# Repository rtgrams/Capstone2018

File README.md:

# Capstone2018

A collection of PCB designs pertaining to the development of a Multi-Room Smart Vent System during the 2017-2018 academic year.

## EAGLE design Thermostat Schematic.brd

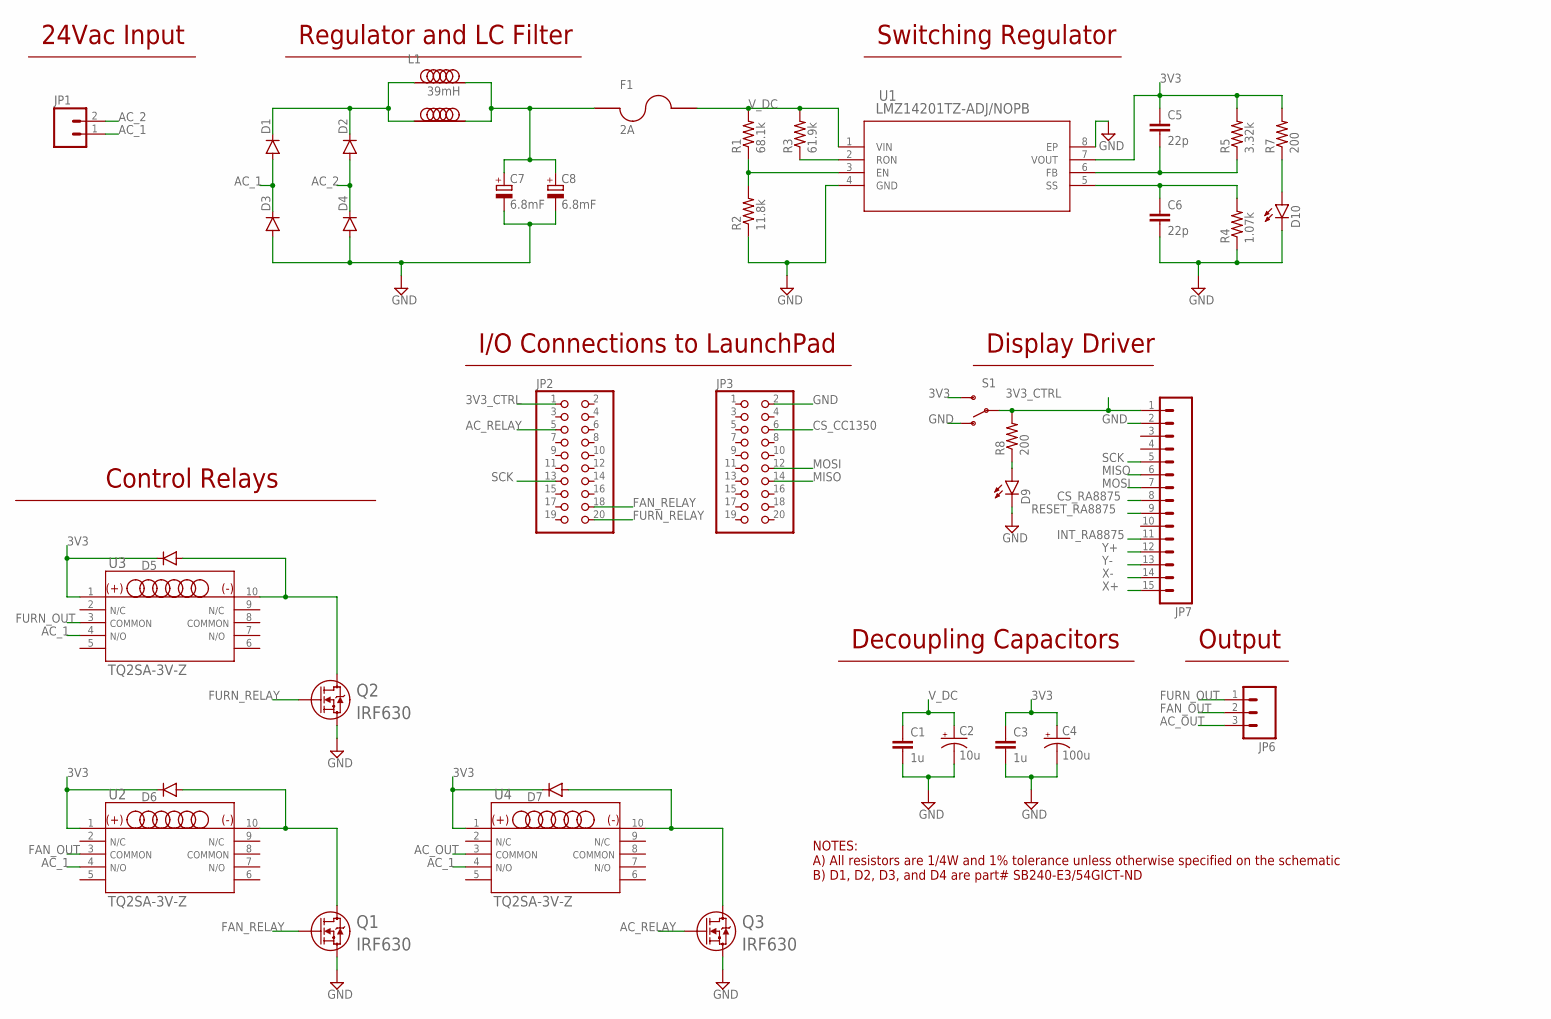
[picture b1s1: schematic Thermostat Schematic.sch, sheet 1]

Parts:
C1, C3: 1u; CAP-PTH-5MM
C2: 10u; CPOL-RADIAL-10UF-25V
C4: 100u; CPOL-RADIAL-1000UF-25V
C5, C6: 22p; CAP-PTH-5MM
C7, C8: 6.8mF; E7,5-16
D1, D2, D3, D4, D5, D6, D7: DIODEPTH; DIODE-1N4001
D9, D10: LED1206; LED-1206
F1: 2A; 36-3550-2-ND
JP1: M023.5MM; SCREWTERMINAL-3.5MM-2
JP2, JP3: PINHD-2X10; 2X10
JP6: M03SCREW; SCREWTERMINAL-3.5MM-3
JP7: M15; 1X15
L1: 39mH; B82733F
Q1, Q2, Q3: IRF630; TO-220
R1: 68.1k; AXIAL-0.3
R2: 11.8k; AXIAL-0.3
R3: 61.9k; AXIAL-0.3
R4: 1.07k; AXIAL-0.3
R5: 3.32k; AXIAL-0.3
R7, R8: 200; AXIAL-0.3
S1: SWITCH-SPDTPTH; SWITCH-SPDT
U1: LMZ14201TZ-ADJ/NOPB; TZA07A
U2, U3, U4: TQ2SA-3V-Z; RELAY_TQ2_SA-M

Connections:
3V3: C3.1, C4.+, C5.1, D5.C, D6.C, D7.C, R5.P$2 (2), R7.P$2 (2), S1.3 (S), U1.7 (VOUT), U2.1, U3.1, U4.1; also elsewhere on the board
3V3_CTRL: JP2.1, JP7.1, R8.P$2 (2), S1.2
AC_1: D1.A, D3.C, JP1.1, U2.4, U3.4, U4.4
AC_2: D2.A, D4.C, JP1.2
AC_OUT: JP6.3, U4.3
AC_RELAY: JP2.5, Q3.1
CS_CC1350: JP3.6; also elsewhere on the board
CS_RA8875: JP7.8; also elsewhere on the board
FAN_OUT: JP6.2, U2.3
FAN_RELAY: JP2.18, Q1.1
FURN_OUT: JP6.1, U3.3
FURN_RELAY: JP2.20, Q2.1
GND: C1.2, C2.2 (-), C3.2, C4.-, C6.2, C7.-, C8.-, D3.A, D4.A, D9.C, D10.C, JP3.2, JP7.2, Q1.3, Q2.3, Q3.3, R2.P$1 (1), R4.P$1 (1), S1.1 (O), U1.4 (GND), U1.8 (EP); also elsewhere on the board
INT_RA8875: JP7.11; also elsewhere on the board
MISO: JP3.14, JP7.6; also elsewhere on the board
MOSI: JP3.12, JP7.7; also elsewhere on the board
unnamed: R1.P$1 (1), R2.P$2 (2), U1.3 (EN)
unnamed: R3.P$1 (1), U1.2 (RON)
unnamed: C5.2, R5.P$1 (1), U1.6 (FB)
unnamed: C6.1, R4.P$2 (2), U1.5 (SS)
unnamed: D9.A, R8.P$1 (1)
unnamed: D1.C, D2.C, L1.P$1, L1.P$4
unnamed: C7.+, C8.+, F1.PIN1A (PIN1), F1.PIN1B (PIN1), L1.P$2, L1.P$3
unnamed: D10.A, R7.P$1 (1)
unnamed: D5.A, Q2.2, U3.10
unnamed: D6.A, Q1.2, U2.10
unnamed: D7.A, Q3.2, U4.10
RESET_RA8875: JP7.9; also elsewhere on the board
SCK: JP2.13, JP7.5; also elsewhere on the board
V_DC: C1.1, C2.1 (+), F1.PIN2A (PIN2), F1.PIN2B (PIN2), R1.P$2 (2), R3.P$2 (2), U1.1 (VIN)
X+: JP7.15; also elsewhere on the board
X-: JP7.14; also elsewhere on the board
Y+: JP7.12; also elsewhere on the board
Y-: JP7.13; also elsewhere on the board

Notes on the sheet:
Decoupling Capacitors
NOTES: A) All resistors are 1/4W and 1% tolerance unless otherwise specified on the schematic B) D1, D2, D3, and D4 are part# SB240-E3/54GICT-ND
I/O Connections to LaunchPad
Regulator and LC Filter
Switching Regulator
24Vac Input
Display Driver
Control Relays
Output

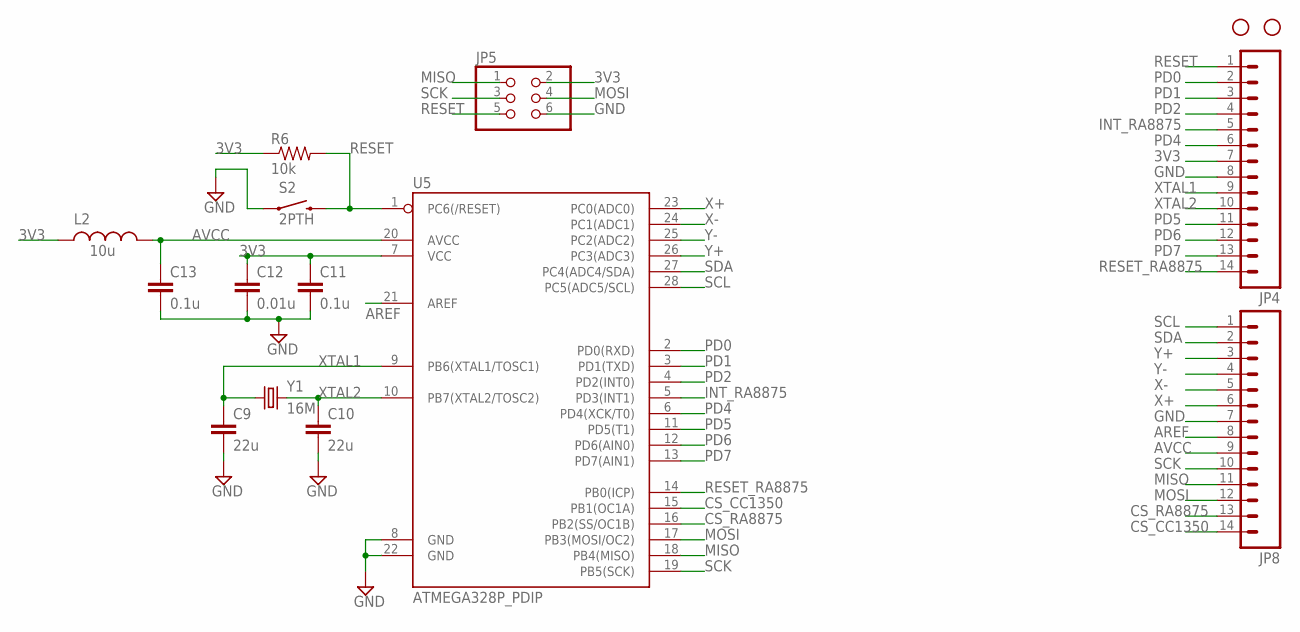
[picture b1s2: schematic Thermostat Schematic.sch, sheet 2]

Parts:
C9, C10: 22u; CAP-PTH-5MM
C11, C13: 0.1u; CAP-PTH-5MM
C12: 0.01u; CAP-PTH-5MM
JP4, JP8: M14; 1X14
JP5: PINHD-2X3; 2X03
L2: 10u; AXIAL-0.6
R6: 10k; AXIAL-0.3
S2: 2PTH; TACTILE-PTH-EZ
STANDOFF3, STANDOFF4: STAND-OFFTIGHT; STAND-OFF-TIGHT
U5: ATMEGA328P_PDIP; DIL28-3
Y1: 16M; HC49US

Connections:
3V3: C11.1, C12.1, JP4.7, JP5.2, L2.P$1 (1), R6.P$1 (1), U5.7 (VCC); also elsewhere on the board
AREF: JP8.8, U5.21 (AREF)
AVCC: C13.1, JP8.9, L2.P$2 (2), U5.20 (AVCC)
CS_CC1350: JP8.14, U5.15 (PB1(OC1A)); also elsewhere on the board
CS_RA8875: JP8.13, U5.16 (PB2(SS/OC1B)); also elsewhere on the board
GND: C9.2, C10.2, C11.2, C12.2, C13.2, JP4.8, JP5.6, JP8.7, S2.1, U5.8 (GND), U5.22 (GND); also elsewhere on the board
INT_RA8875: JP4.5, U5.5 (PD3(INT1)); also elsewhere on the board
MISO: JP5.1, JP8.11, U5.18 (PB4(MISO)); also elsewhere on the board
MOSI: JP5.4, JP8.12, U5.17 (PB3(MOSI/OC2)); also elsewhere on the board
PD0: JP4.2, U5.2 (PD0(RXD))
PD1: JP4.3, U5.3 (PD1(TXD))
PD2: JP4.4, U5.4 (PD2(INT0))
PD4: JP4.6, U5.6 (PD4(XCK/T0))
PD5: JP4.11, U5.11 (PD5(T1))
PD6: JP4.12, U5.12 (PD6(AIN0))
PD7: JP4.13, U5.13 (PD7(AIN1))
RESET: JP4.1, JP5.5, R6.P$2 (2), S2.3 (2), U5.1 (PC6(/RESET))
RESET_RA8875: JP4.14, U5.14 (PB0(ICP)); also elsewhere on the board
SCK: JP5.3, JP8.10, U5.19 (PB5(SCK)); also elsewhere on the board
SCL: JP8.1, U5.28 (PC5(ADC5/SCL))
SDA: JP8.2, U5.27 (PC4(ADC4/SDA))
X+: JP8.6, U5.23 (PC0(ADC0)); also elsewhere on the board
X-: JP8.5, U5.24 (PC1(ADC1)); also elsewhere on the board
XTAL1: C9.1, JP4.9, U5.9 (PB6(XTAL1/TOSC1)), Y1.1
XTAL2: C10.1, JP4.10, U5.10 (PB7(XTAL2/TOSC2)), Y1.2
Y+: JP8.3, U5.26 (PC3(ADC3)); also elsewhere on the board
Y-: JP8.4, U5.25 (PC2(ADC2)); also elsewhere on the board

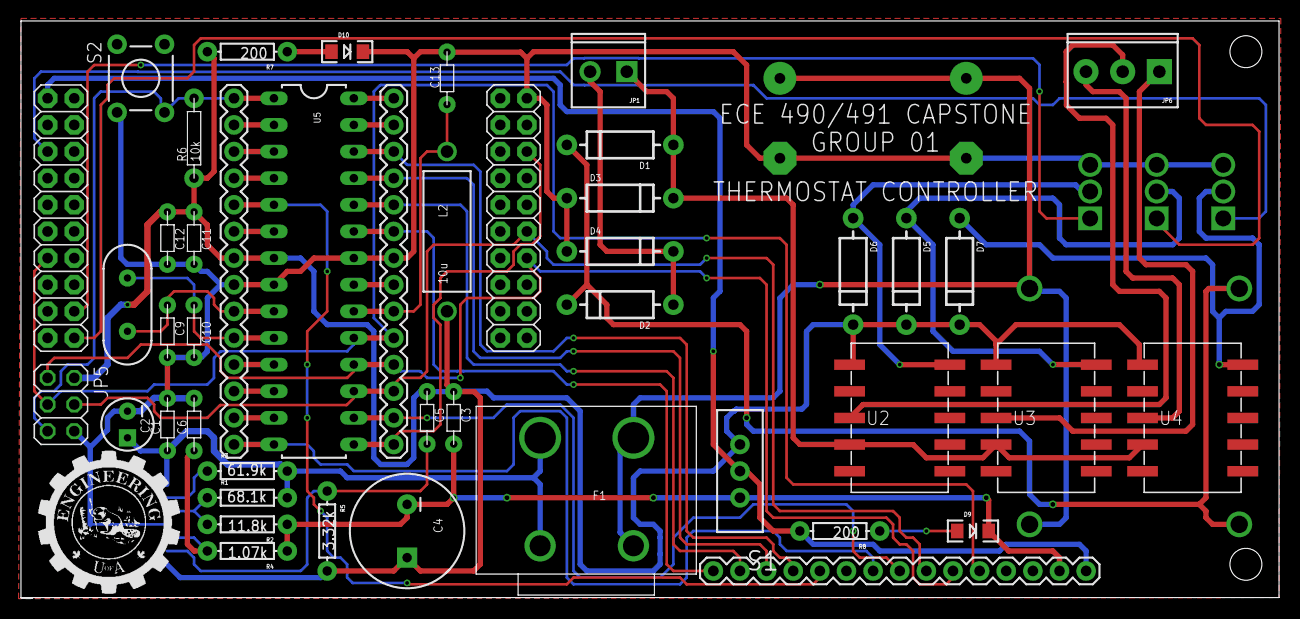
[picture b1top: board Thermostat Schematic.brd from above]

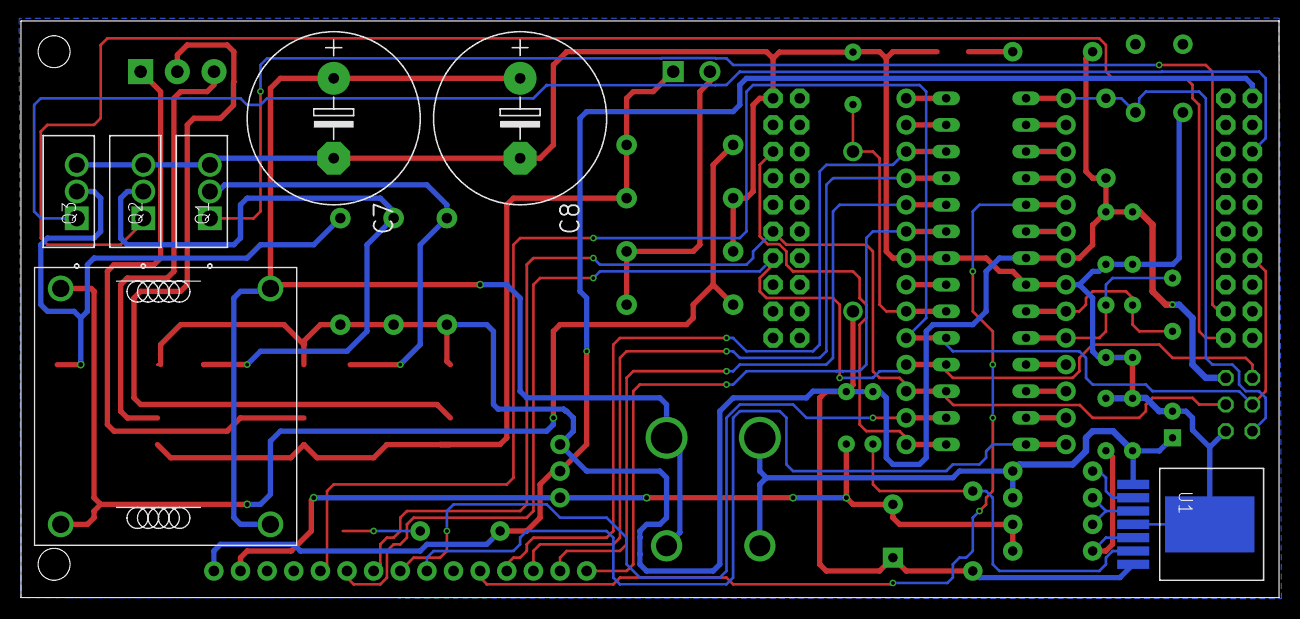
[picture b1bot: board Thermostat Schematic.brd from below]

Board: 2 copper layers, 120.0 x 55.0 mm, 55 parts (7 on the bottom side), 48 nets.

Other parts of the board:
U$1: ENG_LOGO

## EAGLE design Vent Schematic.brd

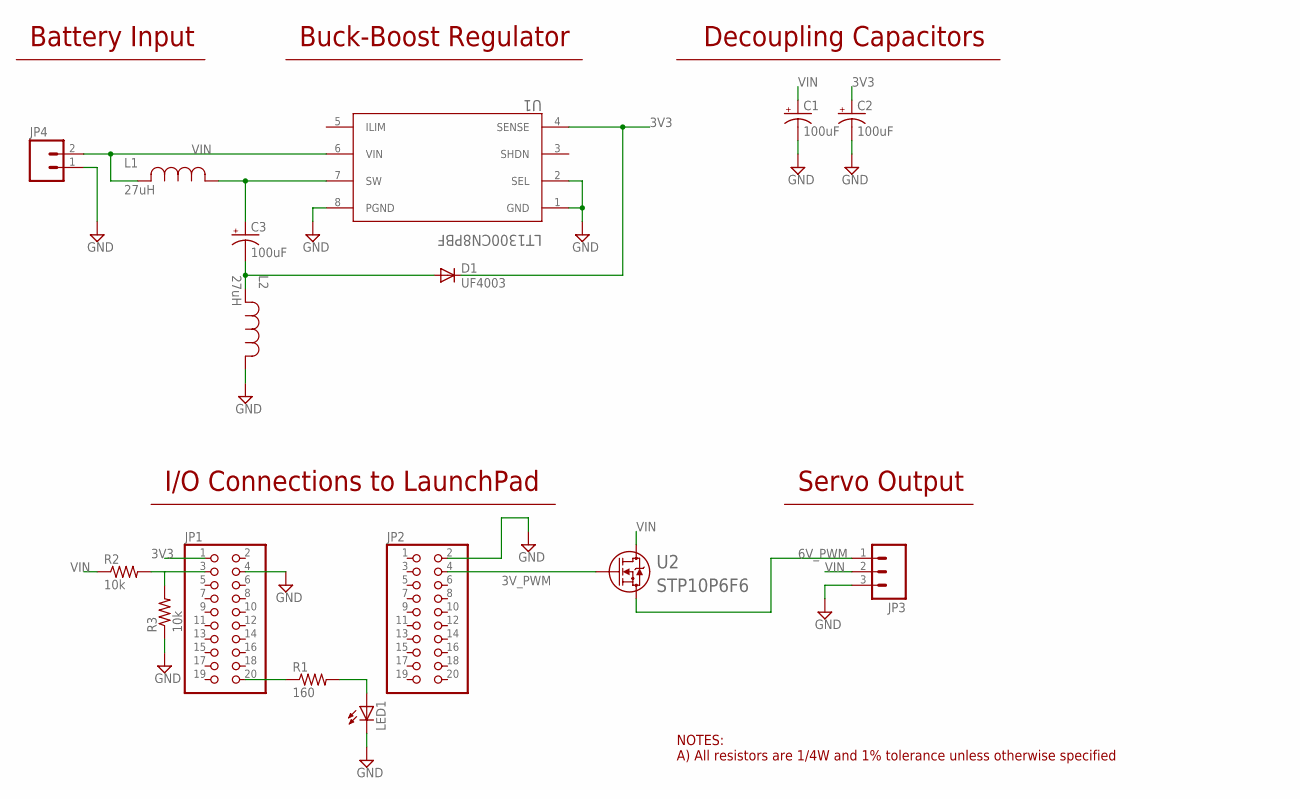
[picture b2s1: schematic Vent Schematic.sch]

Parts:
C1, C2, C3: 100uF; EEU-FR1H101
D1: UF4003; DO41-10
JP1, JP2: PINHD-2X10; 2X10
JP3: M03LOCK_LONGPADS; 1X03_LOCK_LONGPADS
JP4: M023.5MM; SCREWTERMINAL-3.5MM-2
L1, L2: 27uH; IND_2100LL_42_H
LED1: LED5MM
R1: 160; 0603-RES
R2, R3: 10k; 0603-RES
U1: LT1300CN8PBF; PDIP-8_N
U2: STP10P6F6; TO-220

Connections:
3V3: C2.P (+), D1.C, JP1.1, U1.4 (SENSE)
3V_PWM: JP2.4, U2.1
6V_PWM: JP3.1, U2.3
GND: C1.G (-), C2.G (-), JP1.4, JP2.2, JP3.3, JP4.1, L2.1, LED1.K (C), R3.1, U1.1 (GND), U1.2 (SEL), U1.8 (PGND)
unnamed: LED1.A, R1.2
unnamed: JP1.20, R1.1
unnamed: JP1.3, R2.2, R3.2
unnamed: C3.G (-), D1.A, L2.2
unnamed: C3.P (+), L1.1, U1.7 (SW)
VIN: C1.P (+), JP3.2, JP4.2, L1.2, R2.1, U1.6 (VIN), U2.2

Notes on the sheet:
Battery Input
Buck-Boost Regulator
I/O Connections to LaunchPad
Servo Output
Decoupling Capacitors
NOTES: A) All resistors are 1/4W and 1% tolerance unless otherwise specified

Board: 2 copper layers, 16 parts (0 on the bottom side), 10 nets, no tracks yet.

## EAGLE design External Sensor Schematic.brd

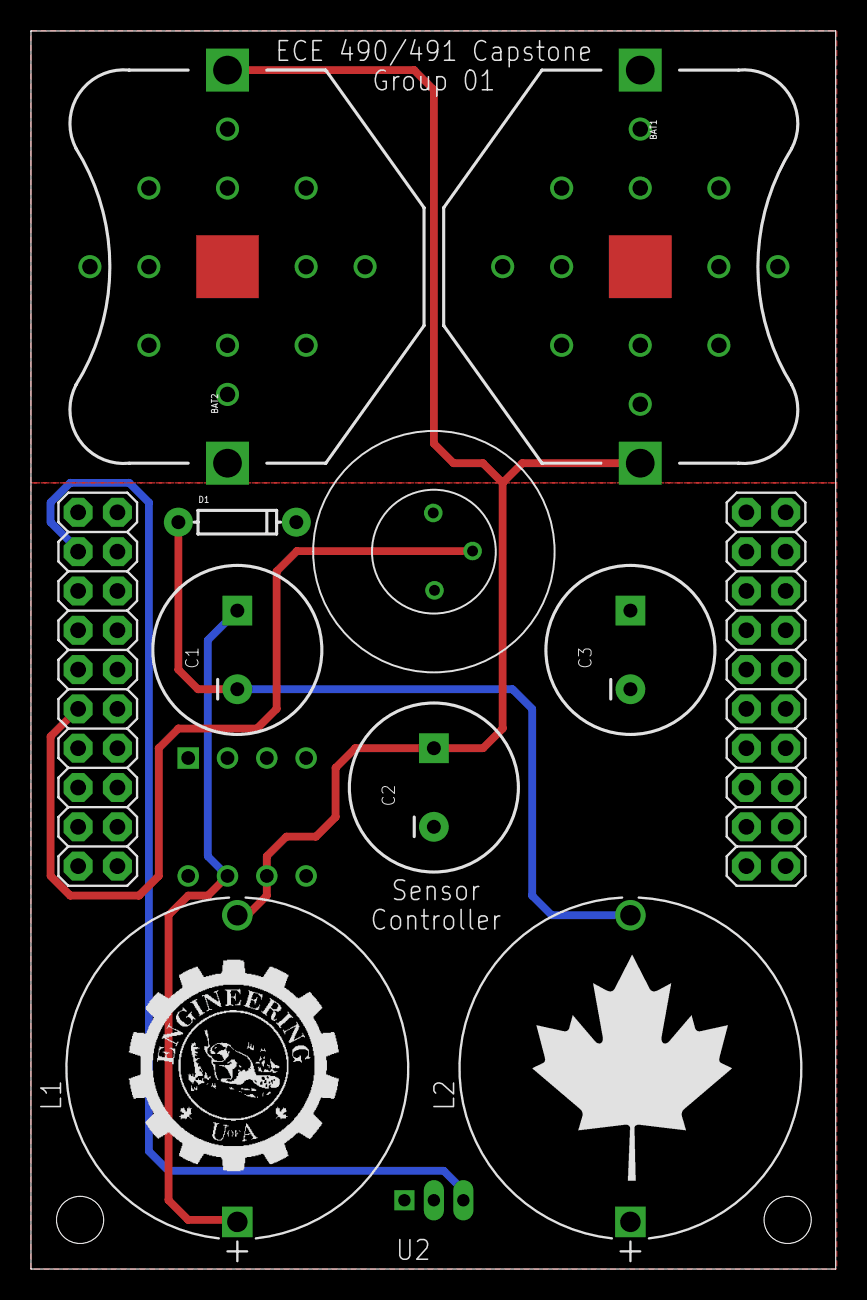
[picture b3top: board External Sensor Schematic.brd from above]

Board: 2 copper layers, 52.0 x 80.0 mm, 17 parts (1 on the bottom side), 7 nets.

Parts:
BAT1, BAT2: 3.6V; BATTCON_245MM_PTH
C1, C2, C3: 100u; CPOL-RADIAL-1000UF-25V
D1: DIODE-1N4148
JP1, JP2: 2X10
L1, L2: 2100LL-270-H-RC; IND_2100LL_42_H
U1: LT1300CN8PBF; PDIP-8_N
U2: LM35CAZ/NOPB; Z03A
U3: PI_SENSOR_255-5419-ND; 255-5419-ND
U$1: ENG_LOGO
U$2: CANADA_FLAG_LOGO
U$3, U$4: STAND-OFF-TIGHT

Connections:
3V3: C3.+, D1.C, JP1.1, U1.4, U2.1, U3.VDD
GND: BAT1.2, BAT2.2, C2.-, C3.-, JP1.4, JP2.2, L2.1, U1.1, U1.2, U1.8, U2.2, U3.GND
unnamed: C1.+, L1.1, U1.7
unnamed: C1.-, D1.A, L2.2
PROXIMITY: JP1.11, U3.VOUT
TEMP: JP1.3, U2.3
VIN: BAT1.3, BAT2.3, C2.+, L1.2, U1.6

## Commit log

2018-01-27 Initial Upload
2018-01-28 Completed Board Layout on all 3
2018-01-28 Fixed Locked File
2018-01-28 Fixed Polygon thermals on Sensor Controller

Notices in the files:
parts and their libraries:
SparkFun-Electromechanical: Licensing: Creative Commons ShareAlike 4.0 International - https://creativecommons.org/licenses/by-sa/4.0
